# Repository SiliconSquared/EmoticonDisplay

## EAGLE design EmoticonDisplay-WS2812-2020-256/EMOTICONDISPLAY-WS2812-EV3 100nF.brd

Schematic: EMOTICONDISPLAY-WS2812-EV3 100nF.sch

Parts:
C1, C2, C3, C4, C5, C6, C7, C8, C9, C10, C11, C12, C13, C14, C15, C16, C17, C18, C19, C20, C21, C22, C23, C24, C25, C26, C27, C28, C29, C30, C31, C32, C33, C34, C35, C36, C37, C38, C39, C40, C41, C42, C43, C44, C45, C46, C47, C48, C49, C50, C51, C52, C53, C54, C55, C56, C57, C58, C59, C60, C61, C62, C63, C64, C65, C66, C67, C68, C69, C70, C71, C72, C73, C74, C75, C76, C77, C78, C79, C80, C81, C82, C83, C84, C85, C86, C87, C88, C89, C90, C91, C92, C93, C94, C95, C96, C97, C98, C99, C100, C101, C102, C103, C104, C105, C106, C107, C108, C109, C110, C111, C112, C113, C114, C115, C116, C117, C118, C119, C120, C121, C122, C123, C124, C125, C126, C127, C128, C129, C130, C131, C132, C133, C134, C135, C136, C137, C138, C139, C140, C141, C142, C143, C144, C145, C146, C147, C148, C149, C150, C151, C152, C153, C154, C155, C156, C157, C158, C159, C160, C161, C162, C163, C164, C165, C166, C167, C168, C169, C170, C171, C172, C173, C174, C175, C176, C177, C178, C179, C180, C181, C182, C183, C184, C185, C186, C187, C188, C189, C190, C191, C192, C193, C194, C195, C196, C197, C198, C199, C200, C201, C202, C203, C204, C205, C206, C207, C208, C209, C210, C211, C212, C213, C214, C215, C216, C217, C218, C219, C220, C221, C222, C223, C224, C225, C226, C227, C228, C229, C230, C231, C232, C233, C234, C235, C236, C237, C238, C239, C240, C241, C242, C243, C244, C245, C246, C247, C248, C249, C250, C251, C252, C253, C254, C255, C256: 100nF; C-0402
CAP15: 1uF 10%; C-0402
FAULT: RED; CHIPLED_0603
GNDA: TPTP15R; TP15R
GNDB: TPTP15R; TP15R
JP2: HEADER-1X5ROUND; 1X05_ROUND
R1: 22k; 0603-NO
R2: 220 1%; 0603-NO
R4: 100k; R0402
R6: 10k; R0402
R8: 1k; R0402
R11: 0; 0603-NO
RGB1, RGB2, RGB3, RGB4, RGB5, RGB6, RGB7, RGB8, RGB9, RGB10, RGB11, RGB12, RGB13, RGB14, RGB15, RGB16, RGB17, RGB18, RGB19, RGB20, RGB21, RGB22, RGB23, RGB24, RGB25, RGB26, RGB27, RGB28, RGB29, RGB30, RGB31, RGB32, RGB33, RGB34, RGB35, RGB36, RGB37, RGB38, RGB39, RGB40, RGB41, RGB42, RGB43, RGB44, RGB45, RGB46, RGB47, RGB48, RGB49, RGB50, RGB51, RGB52, RGB53, RGB54, RGB55, RGB56, RGB57, RGB58, RGB59, RGB60, RGB61, RGB62, RGB63, RGB64, RGB65, RGB66, RGB67, RGB68, RGB69, RGB70, RGB71, RGB72, RGB73, RGB74, RGB75, RGB76, RGB77, RGB78, RGB79, RGB80, RGB81, RGB82, RGB83, RGB84, RGB85, RGB86, RGB87, RGB88, RGB89, RGB90, RGB91, RGB92, RGB93, RGB94, RGB95, RGB96, RGB97, RGB98, RGB99, RGB100, RGB101, RGB102, RGB103, RGB104, RGB105, RGB106, RGB107, RGB108, RGB109, RGB110, RGB111, RGB112, RGB113, RGB114, RGB115, RGB116, RGB117, RGB118, RGB119, RGB120, RGB121, RGB122, RGB123, RGB124, RGB125, RGB126, RGB127, RGB128, RGB129, RGB130, RGB131, RGB132, RGB133, RGB134, RGB135, RGB136, RGB137, RGB138, RGB139, RGB140, RGB141, RGB142, RGB143, RGB144, RGB145, RGB146, RGB147, RGB148, RGB149, RGB150, RGB151, RGB152, RGB153, RGB154, RGB155, RGB156, RGB157, RGB158, RGB159, RGB160, RGB161, RGB162, RGB163, RGB164, RGB165, RGB166, RGB167, RGB168, RGB169, RGB170, RGB171, RGB172, RGB173, RGB174, RGB175, RGB176, RGB177, RGB178, RGB179, RGB180, RGB181, RGB182, RGB183, RGB184, RGB185, RGB186, RGB187, RGB188, RGB189, RGB190, RGB191, RGB192, RGB193, RGB194, RGB195, RGB196, RGB197, RGB198, RGB199, RGB200, RGB201, RGB202, RGB203, RGB204, RGB205, RGB206, RGB207, RGB208, RGB209, RGB210, RGB211, RGB212, RGB213, RGB214, RGB215, RGB216, RGB217, RGB218, RGB219, RGB220, RGB221, RGB222, RGB223, RGB224, RGB225, RGB226, RGB227, RGB228, RGB229, RGB230, RGB231, RGB232, RGB233, RGB234, RGB235, RGB236, RGB237, RGB238, RGB239, RGB240, RGB241, RGB242, RGB243, RGB244, RGB245, RGB246, RGB247, RGB248, RGB249, RGB250, RGB251, RGB252, RGB253, RGB254, RGB255, RGB256: WS2812-2020; LED_WS2812-2020
U1: NCP380LMUAJAATBG; UDFN-6
U2: SN74LVC1T45; SOT23-6
U3: PRTR5V0U2X; SOT-143B

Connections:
ENABLE: JP2.2, R6.1, U1.4 (!EN)
FLAG: FAULT.C, R4.1, U1.3 (!FLAG)
GND: C1.2, C2.2, C3.2, C4.2, C5.2, C6.2, C7.2, C8.2, C9.2, C10.2, C11.2, C12.2, C13.2, C14.2, C15.2, C16.2, C17.2, C18.2, C19.2, C20.2, C21.2, C22.2, C23.2, C24.2, C25.2, C26.2, C27.2, C28.2, C29.2, C30.2, C31.2, C32.2, C33.2, C34.2, C35.2, C36.2, C37.2, C38.2, C39.2, C40.2, C41.2, C42.2, C43.2, C44.2, C45.2, C46.2, C47.2, C48.2, C49.2, C50.2, C51.2, C52.2, C53.2, C54.2, C55.2, C56.2, C57.2, C58.2, C59.2, C60.2, C61.2, C62.2, C63.2, C64.2, C65.2, C66.2, C67.2, C68.2, C69.2, C70.2, C71.2, C72.2, C73.2, C74.2, C75.2, C76.2, C77.2, C78.2, C79.2, C80.2, C81.2, C82.2, C83.2, C84.2, C85.2, C86.2, C87.2, C88.2, C89.2, C90.2, C91.2, C92.2, C93.2, C94.2, C95.2, C96.2, C97.2, C98.2, C99.2, C100.2, C101.2, C102.2, C103.2, C104.2, C105.2, C106.2, C107.2, C108.2, C109.2, C110.2, C111.2, C112.2, C113.2, C114.2, C115.2, C116.2, C117.2, C118.2, C119.2, C120.2, C121.2, C122.2, C123.2, C124.2, C125.2, C126.2, C127.2, C128.2, C129.2, C130.2, C131.2, C132.2, C133.2, C134.2, C135.2, C136.2, C137.2, C138.2, C139.2, C140.2, C141.2, C142.2, C143.2, C144.2, C145.2, C146.2, C147.2, C148.2, C149.2, C150.2, C151.2, C152.2, C153.2, C154.2, C155.2, C156.2, C157.2, C158.2, C159.2, C160.2, C161.2, C162.2, C163.2, C164.2, C165.2, C166.2, C167.2, C168.2, C169.2, C170.2, C171.2, C172.2, C173.2, C174.2, C175.2, C176.2, C177.2, C178.2, C179.2, C180.2, C181.2, C182.2, C183.2, C184.2, C185.2, C186.2, C187.2, C188.2, C189.2, C190.2, C191.2, C192.2, C193.2, C194.2, C195.2, C196.2, C197.2, C198.2, C199.2, C200.2, C201.2, C202.2, C203.2, C204.2, C205.2, C206.2, C207.2, C208.2, C209.2, C210.2, C211.2, C212.2, C213.2, C214.2, C215.2, C216.2, C217.2, C218.2, C219.2, C220.2, C221.2, C222.2, C223.2, C224.2, C225.2, C226.2, C227.2, C228.2, C229.2, C230.2, C231.2, C232.2, C233.2, C234.2, C235.2, C236.2, C237.2, C238.2, C239.2, C240.2, C241.2, C242.2, C243.2, C244.2, C245.2, C246.2, C247.2, C248.2, C249.2, C250.2, C251.2, C252.2, C253.2, C254.2, C255.2, C256.2, CAP15.2, GNDA.TP, GNDB.TP, JP2.4, R1.2, R6.2, RGB1.2 (GND), RGB2.2 (GND), RGB3.2 (GND), RGB4.2 (GND), RGB5.2 (GND), RGB6.2 (GND), RGB7.2 (GND), RGB8.2 (GND), RGB9.2 (GND), RGB10.2 (GND), RGB11.2 (GND), RGB12.2 (GND), RGB13.2 (GND), RGB14.2 (GND), RGB15.2 (GND), RGB16.2 (GND), RGB17.2 (GND), RGB18.2 (GND), RGB19.2 (GND), RGB20.2 (GND), RGB21.2 (GND), RGB22.2 (GND), RGB23.2 (GND), RGB24.2 (GND), RGB25.2 (GND), RGB26.2 (GND), RGB27.2 (GND), RGB28.2 (GND), RGB29.2 (GND), RGB30.2 (GND), RGB31.2 (GND), RGB32.2 (GND), RGB33.2 (GND), RGB34.2 (GND), RGB35.2 (GND), RGB36.2 (GND), RGB37.2 (GND), RGB38.2 (GND), RGB39.2 (GND), RGB40.2 (GND), RGB41.2 (GND), RGB42.2 (GND), RGB43.2 (GND), RGB44.2 (GND), RGB45.2 (GND), RGB46.2 (GND), RGB47.2 (GND), RGB48.2 (GND), RGB49.2 (GND), RGB50.2 (GND), RGB51.2 (GND), RGB52.2 (GND), RGB53.2 (GND), RGB54.2 (GND), RGB55.2 (GND), RGB56.2 (GND), RGB57.2 (GND), RGB58.2 (GND), RGB59.2 (GND), RGB60.2 (GND), RGB61.2 (GND), RGB62.2 (GND), RGB63.2 (GND), RGB64.2 (GND), RGB65.2 (GND), RGB66.2 (GND), RGB67.2 (GND), RGB68.2 (GND), RGB69.2 (GND), RGB70.2 (GND), RGB71.2 (GND), RGB72.2 (GND), RGB73.2 (GND), RGB74.2 (GND), RGB75.2 (GND), RGB76.2 (GND), RGB77.2 (GND), RGB78.2 (GND), RGB79.2 (GND), RGB80.2 (GND), RGB81.2 (GND), RGB82.2 (GND), RGB83.2 (GND), RGB84.2 (GND), RGB85.2 (GND), RGB86.2 (GND), RGB87.2 (GND), RGB88.2 (GND), RGB89.2 (GND), RGB90.2 (GND), RGB91.2 (GND), RGB92.2 (GND), RGB93.2 (GND), RGB94.2 (GND), RGB95.2 (GND), RGB96.2 (GND), RGB97.2 (GND), RGB98.2 (GND), RGB99.2 (GND), RGB100.2 (GND), RGB101.2 (GND), RGB102.2 (GND), RGB103.2 (GND), RGB104.2 (GND), RGB105.2 (GND), RGB106.2 (GND), RGB107.2 (GND), RGB108.2 (GND), RGB109.2 (GND), RGB110.2 (GND), RGB111.2 (GND), RGB112.2 (GND), RGB113.2 (GND), RGB114.2 (GND), RGB115.2 (GND), RGB116.2 (GND), RGB117.2 (GND), RGB118.2 (GND), RGB119.2 (GND), RGB120.2 (GND), RGB121.2 (GND), RGB122.2 (GND), RGB123.2 (GND), RGB124.2 (GND), RGB125.2 (GND), RGB126.2 (GND), RGB127.2 (GND), RGB128.2 (GND), RGB129.2 (GND), RGB130.2 (GND), RGB131.2 (GND), RGB132.2 (GND), RGB133.2 (GND), RGB134.2 (GND), RGB135.2 (GND), RGB136.2 (GND), RGB137.2 (GND), RGB138.2 (GND), RGB139.2 (GND), RGB140.2 (GND), RGB141.2 (GND), RGB142.2 (GND), RGB143.2 (GND), RGB144.2 (GND), RGB145.2 (GND), RGB146.2 (GND), RGB147.2 (GND), RGB148.2 (GND), RGB149.2 (GND), RGB150.2 (GND), RGB151.2 (GND), RGB152.2 (GND), RGB153.2 (GND), RGB154.2 (GND), RGB155.2 (GND), RGB156.2 (GND), RGB157.2 (GND), RGB158.2 (GND), RGB159.2 (GND), RGB160.2 (GND), RGB161.2 (GND), RGB162.2 (GND), RGB163.2 (GND), RGB164.2 (GND), RGB165.2 (GND), RGB166.2 (GND), RGB167.2 (GND), RGB168.2 (GND), RGB169.2 (GND), RGB170.2 (GND), RGB171.2 (GND), RGB172.2 (GND), RGB173.2 (GND), RGB174.2 (GND), RGB175.2 (GND), RGB176.2 (GND), RGB177.2 (GND), RGB178.2 (GND), RGB179.2 (GND), RGB180.2 (GND), RGB181.2 (GND), RGB182.2 (GND), RGB183.2 (GND), RGB184.2 (GND), RGB185.2 (GND), RGB186.2 (GND), RGB187.2 (GND), RGB188.2 (GND), RGB189.2 (GND), RGB190.2 (GND), RGB191.2 (GND), RGB192.2 (GND), RGB193.2 (GND), RGB194.2 (GND), RGB195.2 (GND), RGB196.2 (GND), RGB197.2 (GND), RGB198.2 (GND), RGB199.2 (GND), RGB200.2 (GND), RGB201.2 (GND), RGB202.2 (GND), RGB203.2 (GND), RGB204.2 (GND), RGB205.2 (GND), RGB206.2 (GND), RGB207.2 (GND), RGB208.2 (GND), RGB209.2 (GND), RGB210.2 (GND), RGB211.2 (GND), RGB212.2 (GND), RGB213.2 (GND), RGB214.2 (GND), RGB215.2 (GND), RGB216.2 (GND), RGB217.2 (GND), RGB218.2 (GND), RGB219.2 (GND), RGB220.2 (GND), RGB221.2 (GND), RGB222.2 (GND), RGB223.2 (GND), RGB224.2 (GND), RGB225.2 (GND), RGB226.2 (GND), RGB227.2 (GND), RGB228.2 (GND), RGB229.2 (GND), RGB230.2 (GND), RGB231.2 (GND), RGB232.2 (GND), RGB233.2 (GND), RGB234.2 (GND), RGB235.2 (GND), RGB236.2 (GND), RGB237.2 (GND), RGB238.2 (GND), RGB239.2 (GND), RGB240.2 (GND), RGB241.2 (GND), RGB242.2 (GND), RGB243.2 (GND), RGB244.2 (GND), RGB245.2 (GND), RGB246.2 (GND), RGB247.2 (GND), RGB248.2 (GND), RGB249.2 (GND), RGB250.2 (GND), RGB251.2 (GND), RGB252.2 (GND), RGB253.2 (GND), RGB254.2 (GND), RGB255.2 (GND), RGB256.2 (GND), U1.5 (GND), U1.PAD (GND), U2.2 (GND), U2.5 (DIR), U3.1 (GND)
HOST-PIXDIN: JP2.5, R2.2, U3.3 (IO2)
LLIN-PIXDIN: R2.1, R11.1, U2.4 (B)
unnamed: RGB1.1 (DO), RGB2.3 (DI)
unnamed: RGB2.1 (DO), RGB3.3 (DI)
unnamed: RGB3.1 (DO), RGB4.3 (DI)
unnamed: RGB4.1 (DO), RGB5.3 (DI)
unnamed: RGB5.1 (DO), RGB6.3 (DI)
unnamed: RGB7.1 (DO), RGB8.3 (DI)
unnamed: RGB8.1 (DO), RGB9.3 (DI)
unnamed: RGB9.1 (DO), RGB10.3 (DI)
unnamed: RGB10.1 (DO), RGB11.3 (DI)
unnamed: RGB11.1 (DO), RGB12.3 (DI)
unnamed: RGB12.1 (DO), RGB13.3 (DI)
unnamed: R1.1, U1.2 (ILIM)
unnamed: RGB13.1 (DO), RGB14.3 (DI)
unnamed: RGB14.1 (DO), RGB15.3 (DI)
unnamed: RGB15.1 (DO), RGB16.3 (DI)
unnamed: RGB23.1 (DO), RGB24.3 (DI)
unnamed: RGB6.1 (DO), RGB7.3 (DI)
unnamed: RGB42.1 (DO), RGB43.3 (DI)
unnamed: RGB27.1 (DO), RGB28.3 (DI)
unnamed: RGB18.1 (DO), RGB19.3 (DI)
unnamed: RGB26.1 (DO), RGB27.3 (DI)
unnamed: RGB25.1 (DO), RGB26.3 (DI)
unnamed: RGB24.1 (DO), RGB25.3 (DI)
unnamed: RGB22.1 (DO), RGB23.3 (DI)
unnamed: RGB21.1 (DO), RGB22.3 (DI)
unnamed: RGB20.1 (DO), RGB21.3 (DI)
unnamed: RGB19.1 (DO), RGB20.3 (DI)
unnamed: RGB17.1 (DO), RGB18.3 (DI)
unnamed: RGB16.1 (DO), RGB17.3 (DI)
unnamed: RGB58.1 (DO), RGB59.3 (DI)
unnamed: RGB41.1 (DO), RGB42.3 (DI)
unnamed: RGB40.1 (DO), RGB41.3 (DI)
unnamed: RGB39.1 (DO), RGB40.3 (DI)
unnamed: RGB38.1 (DO), RGB39.3 (DI)
unnamed: RGB37.1 (DO), RGB38.3 (DI)
unnamed: RGB36.1 (DO), RGB37.3 (DI)
unnamed: RGB35.1 (DO), RGB36.3 (DI)
unnamed: RGB34.1 (DO), RGB35.3 (DI)
unnamed: RGB33.1 (DO), RGB34.3 (DI)
unnamed: RGB32.1 (DO), RGB33.3 (DI)
unnamed: RGB31.1 (DO), RGB32.3 (DI)
unnamed: RGB30.1 (DO), RGB31.3 (DI)
unnamed: RGB29.1 (DO), RGB30.3 (DI)
unnamed: RGB28.1 (DO), RGB29.3 (DI)
unnamed: RGB43.1 (DO), RGB44.3 (DI)
unnamed: RGB44.1 (DO), RGB45.3 (DI)
unnamed: RGB45.1 (DO), RGB46.3 (DI)
unnamed: RGB46.1 (DO), RGB47.3 (DI)
unnamed: RGB47.1 (DO), RGB48.3 (DI)
unnamed: RGB48.1 (DO), RGB49.3 (DI)
unnamed: RGB49.1 (DO), RGB50.3 (DI)
unnamed: RGB50.1 (DO), RGB51.3 (DI)
unnamed: RGB51.1 (DO), RGB52.3 (DI)
unnamed: RGB52.1 (DO), RGB53.3 (DI)
unnamed: RGB53.1 (DO), RGB54.3 (DI)
unnamed: RGB54.1 (DO), RGB55.3 (DI)
unnamed: RGB55.1 (DO), RGB56.3 (DI)
unnamed: RGB56.1 (DO), RGB57.3 (DI)
unnamed: RGB75.1 (DO), RGB76.3 (DI)
unnamed: RGB59.1 (DO), RGB60.3 (DI)
unnamed: RGB57.1 (DO), RGB58.3 (DI)
unnamed: RGB60.1 (DO), RGB61.3 (DI)
unnamed: RGB61.1 (DO), RGB62.3 (DI)
unnamed: RGB62.1 (DO), RGB63.3 (DI)
unnamed: RGB63.1 (DO), RGB64.3 (DI)
unnamed: RGB64.1 (DO), RGB65.3 (DI)
unnamed: RGB65.1 (DO), RGB66.3 (DI)
unnamed: RGB66.1 (DO), RGB67.3 (DI)
unnamed: RGB67.1 (DO), RGB68.3 (DI)
unnamed: RGB68.1 (DO), RGB69.3 (DI)
unnamed: RGB69.1 (DO), RGB70.3 (DI)
unnamed: RGB70.1 (DO), RGB71.3 (DI)
unnamed: RGB71.1 (DO), RGB72.3 (DI)
unnamed: RGB72.1 (DO), RGB73.3 (DI)
unnamed: RGB73.1 (DO), RGB74.3 (DI)
unnamed: RGB74.1 (DO), RGB75.3 (DI)
unnamed: RGB121.1 (DO), RGB122.3 (DI)
unnamed: RGB122.1 (DO), RGB123.3 (DI)
unnamed: RGB76.1 (DO), RGB77.3 (DI)
unnamed: RGB77.1 (DO), RGB78.3 (DI)
unnamed: RGB78.1 (DO), RGB79.3 (DI)
unnamed: RGB79.1 (DO), RGB80.3 (DI)
unnamed: RGB80.1 (DO), RGB81.3 (DI)
unnamed: RGB81.1 (DO), RGB82.3 (DI)
unnamed: RGB82.1 (DO), RGB83.3 (DI)
unnamed: RGB83.1 (DO), RGB84.3 (DI)
unnamed: RGB84.1 (DO), RGB85.3 (DI)
unnamed: RGB85.1 (DO), RGB86.3 (DI)
unnamed: RGB86.1 (DO), RGB87.3 (DI)
unnamed: RGB87.1 (DO), RGB88.3 (DI)
unnamed: RGB88.1 (DO), RGB89.3 (DI)
unnamed: RGB89.1 (DO), RGB90.3 (DI)
unnamed: RGB90.1 (DO), RGB91.3 (DI)
unnamed: RGB91.1 (DO), RGB92.3 (DI)
unnamed: RGB123.1 (DO), RGB124.3 (DI)
unnamed: RGB93.1 (DO), RGB94.3 (DI)
unnamed: RGB94.1 (DO), RGB95.3 (DI)
unnamed: RGB95.1 (DO), RGB96.3 (DI)
unnamed: RGB96.1 (DO), RGB97.3 (DI)
unnamed: RGB97.1 (DO), RGB98.3 (DI)
unnamed: RGB98.1 (DO), RGB99.3 (DI)
unnamed: RGB99.1 (DO), RGB100.3 (DI)
unnamed: RGB100.1 (DO), RGB101.3 (DI)
unnamed: RGB101.1 (DO), RGB102.3 (DI)
unnamed: RGB102.1 (DO), RGB103.3 (DI)
unnamed: RGB103.1 (DO), RGB104.3 (DI)
unnamed: RGB104.1 (DO), RGB105.3 (DI)
unnamed: RGB105.1 (DO), RGB106.3 (DI)
unnamed: RGB106.1 (DO), RGB107.3 (DI)
unnamed: RGB107.1 (DO), RGB108.3 (DI)
unnamed: RGB108.1 (DO), RGB109.3 (DI)
unnamed: RGB109.1 (DO), RGB110.3 (DI)
unnamed: RGB198.1 (DO), RGB199.3 (DI)
unnamed: RGB92.1 (DO), RGB93.3 (DI)
unnamed: RGB124.1 (DO), RGB125.3 (DI)
unnamed: RGB111.1 (DO), RGB112.3 (DI)
unnamed: RGB112.1 (DO), RGB113.3 (DI)
unnamed: RGB113.1 (DO), RGB114.3 (DI)
unnamed: RGB114.1 (DO), RGB115.3 (DI)
unnamed: RGB115.1 (DO), RGB116.3 (DI)
unnamed: RGB116.1 (DO), RGB117.3 (DI)
unnamed: RGB117.1 (DO), RGB118.3 (DI)
unnamed: RGB118.1 (DO), RGB119.3 (DI)
unnamed: RGB119.1 (DO), RGB120.3 (DI)
unnamed: RGB120.1 (DO), RGB121.3 (DI)
unnamed: RGB125.1 (DO), RGB126.3 (DI)
unnamed: RGB126.1 (DO), RGB127.3 (DI)
unnamed: RGB127.1 (DO), RGB128.3 (DI)
unnamed: RGB110.1 (DO), RGB111.3 (DI)
unnamed: RGB164.1 (DO), RGB165.3 (DI)
unnamed: RGB214.1 (DO), RGB215.3 (DI)
unnamed: RGB147.1 (DO), RGB148.3 (DI)
unnamed: RGB129.1 (DO), RGB130.3 (DI)
unnamed: RGB130.1 (DO), RGB131.3 (DI)
unnamed: RGB131.1 (DO), RGB132.3 (DI)
unnamed: RGB132.1 (DO), RGB133.3 (DI)
unnamed: RGB133.1 (DO), RGB134.3 (DI)
unnamed: RGB134.1 (DO), RGB135.3 (DI)
unnamed: RGB135.1 (DO), RGB136.3 (DI)
unnamed: RGB136.1 (DO), RGB137.3 (DI)
unnamed: RGB137.1 (DO), RGB138.3 (DI)
unnamed: RGB138.1 (DO), RGB139.3 (DI)
unnamed: RGB139.1 (DO), RGB140.3 (DI)
unnamed: RGB140.1 (DO), RGB141.3 (DI)
unnamed: RGB141.1 (DO), RGB142.3 (DI)
unnamed: RGB142.1 (DO), RGB143.3 (DI)
unnamed: RGB143.1 (DO), RGB144.3 (DI)
unnamed: RGB144.1 (DO), RGB145.3 (DI)
unnamed: RGB145.1 (DO), RGB146.3 (DI)
unnamed: RGB128.1 (DO), RGB129.3 (DI)
unnamed: RGB148.1 (DO), RGB149.3 (DI)
unnamed: RGB149.1 (DO), RGB150.3 (DI)
unnamed: RGB150.1 (DO), RGB151.3 (DI)
unnamed: RGB151.1 (DO), RGB152.3 (DI)
unnamed: RGB152.1 (DO), RGB153.3 (DI)
unnamed: RGB153.1 (DO), RGB154.3 (DI)
unnamed: RGB154.1 (DO), RGB155.3 (DI)
unnamed: RGB155.1 (DO), RGB156.3 (DI)
unnamed: RGB156.1 (DO), RGB157.3 (DI)
unnamed: RGB157.1 (DO), RGB158.3 (DI)
unnamed: RGB158.1 (DO), RGB159.3 (DI)
unnamed: RGB159.1 (DO), RGB160.3 (DI)
unnamed: RGB160.1 (DO), RGB161.3 (DI)
unnamed: RGB161.1 (DO), RGB162.3 (DI)
unnamed: RGB162.1 (DO), RGB163.3 (DI)
unnamed: RGB163.1 (DO), RGB164.3 (DI)
unnamed: RGB146.1 (DO), RGB147.3 (DI)
unnamed: RGB165.1 (DO), RGB166.3 (DI)
unnamed: RGB166.1 (DO), RGB167.3 (DI)
unnamed: RGB167.1 (DO), RGB168.3 (DI)
unnamed: RGB168.1 (DO), RGB169.3 (DI)
unnamed: RGB169.1 (DO), RGB170.3 (DI)
unnamed: RGB170.1 (DO), RGB171.3 (DI)
unnamed: RGB171.1 (DO), RGB172.3 (DI)
unnamed: RGB172.1 (DO), RGB173.3 (DI)
unnamed: RGB173.1 (DO), RGB174.3 (DI)
unnamed: RGB174.1 (DO), RGB175.3 (DI)
unnamed: RGB175.1 (DO), RGB176.3 (DI)
unnamed: RGB176.1 (DO), RGB177.3 (DI)
unnamed: RGB177.1 (DO), RGB178.3 (DI)
unnamed: RGB178.1 (DO), RGB179.3 (DI)
unnamed: RGB179.1 (DO), RGB180.3 (DI)
unnamed: RGB180.1 (DO), RGB181.3 (DI)
unnamed: RGB181.1 (DO), RGB182.3 (DI)
unnamed: RGB230.1 (DO), RGB231.3 (DI)
unnamed: RGB183.1 (DO), RGB184.3 (DI)
unnamed: RGB184.1 (DO), RGB185.3 (DI)
unnamed: RGB185.1 (DO), RGB186.3 (DI)
unnamed: RGB186.1 (DO), RGB187.3 (DI)
unnamed: RGB187.1 (DO), RGB188.3 (DI)
unnamed: RGB188.1 (DO), RGB189.3 (DI)
unnamed: RGB189.1 (DO), RGB190.3 (DI)
unnamed: RGB190.1 (DO), RGB191.3 (DI)
unnamed: RGB191.1 (DO), RGB192.3 (DI)
unnamed: RGB192.1 (DO), RGB193.3 (DI)
unnamed: RGB193.1 (DO), RGB194.3 (DI)
unnamed: RGB194.1 (DO), RGB195.3 (DI)
unnamed: RGB195.1 (DO), RGB196.3 (DI)
unnamed: RGB196.1 (DO), RGB197.3 (DI)
unnamed: RGB197.1 (DO), RGB198.3 (DI)
unnamed: RGB182.1 (DO), RGB183.3 (DI)
unnamed: RGB199.1 (DO), RGB200.3 (DI)
unnamed: RGB200.1 (DO), RGB201.3 (DI)
unnamed: RGB201.1 (DO), RGB202.3 (DI)
unnamed: RGB202.1 (DO), RGB203.3 (DI)
unnamed: RGB203.1 (DO), RGB204.3 (DI)
unnamed: RGB204.1 (DO), RGB205.3 (DI)
unnamed: RGB205.1 (DO), RGB206.3 (DI)
unnamed: RGB206.1 (DO), RGB207.3 (DI)
unnamed: RGB207.1 (DO), RGB208.3 (DI)
unnamed: RGB208.1 (DO), RGB209.3 (DI)
unnamed: RGB209.1 (DO), RGB210.3 (DI)
unnamed: RGB210.1 (DO), RGB211.3 (DI)
unnamed: RGB211.1 (DO), RGB212.3 (DI)
unnamed: RGB212.1 (DO), RGB213.3 (DI)
unnamed: RGB213.1 (DO), RGB214.3 (DI)
unnamed: RGB215.1 (DO), RGB216.3 (DI)
unnamed: RGB216.1 (DO), RGB217.3 (DI)
unnamed: RGB217.1 (DO), RGB218.3 (DI)
unnamed: RGB218.1 (DO), RGB219.3 (DI)
unnamed: RGB219.1 (DO), RGB220.3 (DI)
unnamed: RGB220.1 (DO), RGB221.3 (DI)
unnamed: RGB221.1 (DO), RGB222.3 (DI)
unnamed: RGB222.1 (DO), RGB223.3 (DI)
unnamed: RGB223.1 (DO), RGB224.3 (DI)
unnamed: RGB224.1 (DO), RGB225.3 (DI)
unnamed: RGB225.1 (DO), RGB226.3 (DI)
unnamed: RGB226.1 (DO), RGB227.3 (DI)
unnamed: RGB227.1 (DO), RGB228.3 (DI)
unnamed: RGB231.1 (DO), RGB232.3 (DI)
unnamed: RGB229.1 (DO), RGB230.3 (DI)
unnamed: RGB232.1 (DO), RGB233.3 (DI)
unnamed: RGB233.1 (DO), RGB234.3 (DI)
unnamed: RGB234.1 (DO), RGB235.3 (DI)
unnamed: RGB235.1 (DO), RGB236.3 (DI)
unnamed: RGB236.1 (DO), RGB237.3 (DI)
unnamed: RGB237.1 (DO), RGB238.3 (DI)
unnamed: RGB238.1 (DO), RGB239.3 (DI)
unnamed: RGB239.1 (DO), RGB240.3 (DI)
unnamed: RGB228.1 (DO), RGB229.3 (DI)
unnamed: RGB240.1 (DO), RGB241.3 (DI)
unnamed: FAULT.A, R8.2
unnamed: RGB241.1 (DO), RGB242.3 (DI)
unnamed: RGB242.1 (DO), RGB243.3 (DI)
unnamed: RGB243.1 (DO), RGB244.3 (DI)
unnamed: RGB244.1 (DO), RGB245.3 (DI)
unnamed: RGB245.1 (DO), RGB246.3 (DI)
unnamed: RGB246.1 (DO), RGB247.3 (DI)
unnamed: RGB247.1 (DO), RGB248.3 (DI)
unnamed: RGB248.1 (DO), RGB249.3 (DI)
unnamed: RGB249.1 (DO), RGB250.3 (DI)
unnamed: RGB251.1 (DO), RGB252.3 (DI)
unnamed: RGB252.1 (DO), RGB253.3 (DI)
unnamed: RGB253.1 (DO), RGB254.3 (DI)
unnamed: RGB254.1 (DO), RGB255.3 (DI)
unnamed: RGB255.1 (DO), RGB256.3 (DI)
unnamed: RGB250.1 (DO), RGB251.3 (DI)
PIXDIN: R11.2, RGB1.3 (DI), U2.3 (A)
VDD: C1.1, C2.1, C3.1, C4.1, C5.1, C6.1, C7.1, C8.1, C9.1, C10.1, C11.1, C12.1, C13.1, C14.1, C15.1, C16.1, C17.1, C18.1, C19.1, C20.1, C21.1, C22.1, C23.1, C24.1, C25.1, C26.1, C27.1, C28.1, C29.1, C30.1, C31.1, C32.1, C33.1, C34.1, C35.1, C36.1, C37.1, C38.1, C39.1, C40.1, C41.1, C42.1, C43.1, C44.1, C45.1, C46.1, C47.1, C48.1, C49.1, C50.1, C51.1, C52.1, C53.1, C54.1, C55.1, C56.1, C57.1, C58.1, C59.1, C60.1, C61.1, C62.1, C63.1, C64.1, C65.1, C66.1, C67.1, C68.1, C69.1, C70.1, C71.1, C72.1, C73.1, C74.1, C75.1, C76.1, C77.1, C78.1, C79.1, C80.1, C81.1, C82.1, C83.1, C84.1, C85.1, C86.1, C87.1, C88.1, C89.1, C90.1, C91.1, C92.1, C93.1, C94.1, C95.1, C96.1, C97.1, C98.1, C99.1, C100.1, C101.1, C102.1, C103.1, C104.1, C105.1, C106.1, C107.1, C108.1, C109.1, C110.1, C111.1, C112.1, C113.1, C114.1, C115.1, C116.1, C117.1, C118.1, C119.1, C120.1, C121.1, C122.1, C123.1, C124.1, C125.1, C126.1, C127.1, C128.1, C129.1, C130.1, C131.1, C132.1, C133.1, C134.1, C135.1, C136.1, C137.1, C138.1, C139.1, C140.1, C141.1, C142.1, C143.1, C144.1, C145.1, C146.1, C147.1, C148.1, C149.1, C150.1, C151.1, C152.1, C153.1, C154.1, C155.1, C156.1, C157.1, C158.1, C159.1, C160.1, C161.1, C162.1, C163.1, C164.1, C165.1, C166.1, C167.1, C168.1, C169.1, C170.1, C171.1, C172.1, C173.1, C174.1, C175.1, C176.1, C177.1, C178.1, C179.1, C180.1, C181.1, C182.1, C183.1, C184.1, C185.1, C186.1, C187.1, C188.1, C189.1, C190.1, C191.1, C192.1, C193.1, C194.1, C195.1, C196.1, C197.1, C198.1, C199.1, C200.1, C201.1, C202.1, C203.1, C204.1, C205.1, C206.1, C207.1, C208.1, C209.1, C210.1, C211.1, C212.1, C213.1, C214.1, C215.1, C216.1, C217.1, C218.1, C219.1, C220.1, C221.1, C222.1, C223.1, C224.1, C225.1, C226.1, C227.1, C228.1, C229.1, C230.1, C231.1, C232.1, C233.1, C234.1, C235.1, C236.1, C237.1, C238.1, C239.1, C240.1, C241.1, C242.1, C243.1, C244.1, C245.1, C246.1, C247.1, C248.1, C249.1, C250.1, C251.1, C252.1, C253.1, C254.1, C255.1, C256.1, RGB1.4 (VDD), RGB2.4 (VDD), RGB3.4 (VDD), RGB4.4 (VDD), RGB5.4 (VDD), RGB6.4 (VDD), RGB7.4 (VDD), RGB8.4 (VDD), RGB9.4 (VDD), RGB10.4 (VDD), RGB11.4 (VDD), RGB12.4 (VDD), RGB13.4 (VDD), RGB14.4 (VDD), RGB15.4 (VDD), RGB16.4 (VDD), RGB17.4 (VDD), RGB18.4 (VDD), RGB19.4 (VDD), RGB20.4 (VDD), RGB21.4 (VDD), RGB22.4 (VDD), RGB23.4 (VDD), RGB24.4 (VDD), RGB25.4 (VDD), RGB26.4 (VDD), RGB27.4 (VDD), RGB28.4 (VDD), RGB29.4 (VDD), RGB30.4 (VDD), RGB31.4 (VDD), RGB32.4 (VDD), RGB33.4 (VDD), RGB34.4 (VDD), RGB35.4 (VDD), RGB36.4 (VDD), RGB37.4 (VDD), RGB38.4 (VDD), RGB39.4 (VDD), RGB40.4 (VDD), RGB41.4 (VDD), RGB42.4 (VDD), RGB43.4 (VDD), RGB44.4 (VDD), RGB45.4 (VDD), RGB46.4 (VDD), RGB47.4 (VDD), RGB48.4 (VDD), RGB49.4 (VDD), RGB50.4 (VDD), RGB51.4 (VDD), RGB52.4 (VDD), RGB53.4 (VDD), RGB54.4 (VDD), RGB55.4 (VDD), RGB56.4 (VDD), RGB57.4 (VDD), RGB58.4 (VDD), RGB59.4 (VDD), RGB60.4 (VDD), RGB61.4 (VDD), RGB62.4 (VDD), RGB63.4 (VDD), RGB64.4 (VDD), RGB65.4 (VDD), RGB66.4 (VDD), RGB67.4 (VDD), RGB68.4 (VDD), RGB69.4 (VDD), RGB70.4 (VDD), RGB71.4 (VDD), RGB72.4 (VDD), RGB73.4 (VDD), RGB74.4 (VDD), RGB75.4 (VDD), RGB76.4 (VDD), RGB77.4 (VDD), RGB78.4 (VDD), RGB79.4 (VDD), RGB80.4 (VDD), RGB81.4 (VDD), RGB82.4 (VDD), RGB83.4 (VDD), RGB84.4 (VDD), RGB85.4 (VDD), RGB86.4 (VDD), RGB87.4 (VDD), RGB88.4 (VDD), RGB89.4 (VDD), RGB90.4 (VDD), RGB91.4 (VDD), RGB92.4 (VDD), RGB93.4 (VDD), RGB94.4 (VDD), RGB95.4 (VDD), RGB96.4 (VDD), RGB97.4 (VDD), RGB98.4 (VDD), RGB99.4 (VDD), RGB100.4 (VDD), RGB101.4 (VDD), RGB102.4 (VDD), RGB103.4 (VDD), RGB104.4 (VDD), RGB105.4 (VDD), RGB106.4 (VDD), RGB107.4 (VDD), RGB108.4 (VDD), RGB109.4 (VDD), RGB110.4 (VDD), RGB111.4 (VDD), RGB112.4 (VDD), RGB113.4 (VDD), RGB114.4 (VDD), RGB115.4 (VDD), RGB116.4 (VDD), RGB117.4 (VDD), RGB118.4 (VDD), RGB119.4 (VDD), RGB120.4 (VDD), RGB121.4 (VDD), RGB122.4 (VDD), RGB123.4 (VDD), RGB124.4 (VDD), RGB125.4 (VDD), RGB126.4 (VDD), RGB127.4 (VDD), RGB128.4 (VDD), RGB129.4 (VDD), RGB130.4 (VDD), RGB131.4 (VDD), RGB132.4 (VDD), RGB133.4 (VDD), RGB134.4 (VDD), RGB135.4 (VDD), RGB136.4 (VDD), RGB137.4 (VDD), RGB138.4 (VDD), RGB139.4 (VDD), RGB140.4 (VDD), RGB141.4 (VDD), RGB142.4 (VDD), RGB143.4 (VDD), RGB144.4 (VDD), RGB145.4 (VDD), RGB146.4 (VDD), RGB147.4 (VDD), RGB148.4 (VDD), RGB149.4 (VDD), RGB150.4 (VDD), RGB151.4 (VDD), RGB152.4 (VDD), RGB153.4 (VDD), RGB154.4 (VDD), RGB155.4 (VDD), RGB156.4 (VDD), RGB157.4 (VDD), RGB158.4 (VDD), RGB159.4 (VDD), RGB160.4 (VDD), RGB161.4 (VDD), RGB162.4 (VDD), RGB163.4 (VDD), RGB164.4 (VDD), RGB165.4 (VDD), RGB166.4 (VDD), RGB167.4 (VDD), RGB168.4 (VDD), RGB169.4 (VDD), RGB170.4 (VDD), RGB171.4 (VDD), RGB172.4 (VDD), RGB173.4 (VDD), RGB174.4 (VDD), RGB175.4 (VDD), RGB176.4 (VDD), RGB177.4 (VDD), RGB178.4 (VDD), RGB179.4 (VDD), RGB180.4 (VDD), RGB181.4 (VDD), RGB182.4 (VDD), RGB183.4 (VDD), RGB184.4 (VDD), RGB185.4 (VDD), RGB186.4 (VDD), RGB187.4 (VDD), RGB188.4 (VDD), RGB189.4 (VDD), RGB190.4 (VDD), RGB191.4 (VDD), RGB192.4 (VDD), RGB193.4 (VDD), RGB194.4 (VDD), RGB195.4 (VDD), RGB196.4 (VDD), RGB197.4 (VDD), RGB198.4 (VDD), RGB199.4 (VDD), RGB200.4 (VDD), RGB201.4 (VDD), RGB202.4 (VDD), RGB203.4 (VDD), RGB204.4 (VDD), RGB205.4 (VDD), RGB206.4 (VDD), RGB207.4 (VDD), RGB208.4 (VDD), RGB209.4 (VDD), RGB210.4 (VDD), RGB211.4 (VDD), RGB212.4 (VDD), RGB213.4 (VDD), RGB214.4 (VDD), RGB215.4 (VDD), RGB216.4 (VDD), RGB217.4 (VDD), RGB218.4 (VDD), RGB219.4 (VDD), RGB220.4 (VDD), RGB221.4 (VDD), RGB222.4 (VDD), RGB223.4 (VDD), RGB224.4 (VDD), RGB225.4 (VDD), RGB226.4 (VDD), RGB227.4 (VDD), RGB228.4 (VDD), RGB229.4 (VDD), RGB230.4 (VDD), RGB231.4 (VDD), RGB232.4 (VDD), RGB233.4 (VDD), RGB234.4 (VDD), RGB235.4 (VDD), RGB236.4 (VDD), RGB237.4 (VDD), RGB238.4 (VDD), RGB239.4 (VDD), RGB240.4 (VDD), RGB241.4 (VDD), RGB242.4 (VDD), RGB243.4 (VDD), RGB244.4 (VDD), RGB245.4 (VDD), RGB246.4 (VDD), RGB247.4 (VDD), RGB248.4 (VDD), RGB249.4 (VDD), RGB250.4 (VDD), RGB251.4 (VDD), RGB252.4 (VDD), RGB253.4 (VDD), RGB254.4 (VDD), RGB255.4 (VDD), RGB256.4 (VDD), U1.1 (VOUT), U2.1 (VCCA), U2.6 (VCCB), U3.4 (VCC)
VHOST: CAP15.1, JP2.1, R4.2, R8.1, U1.6 (VIN)

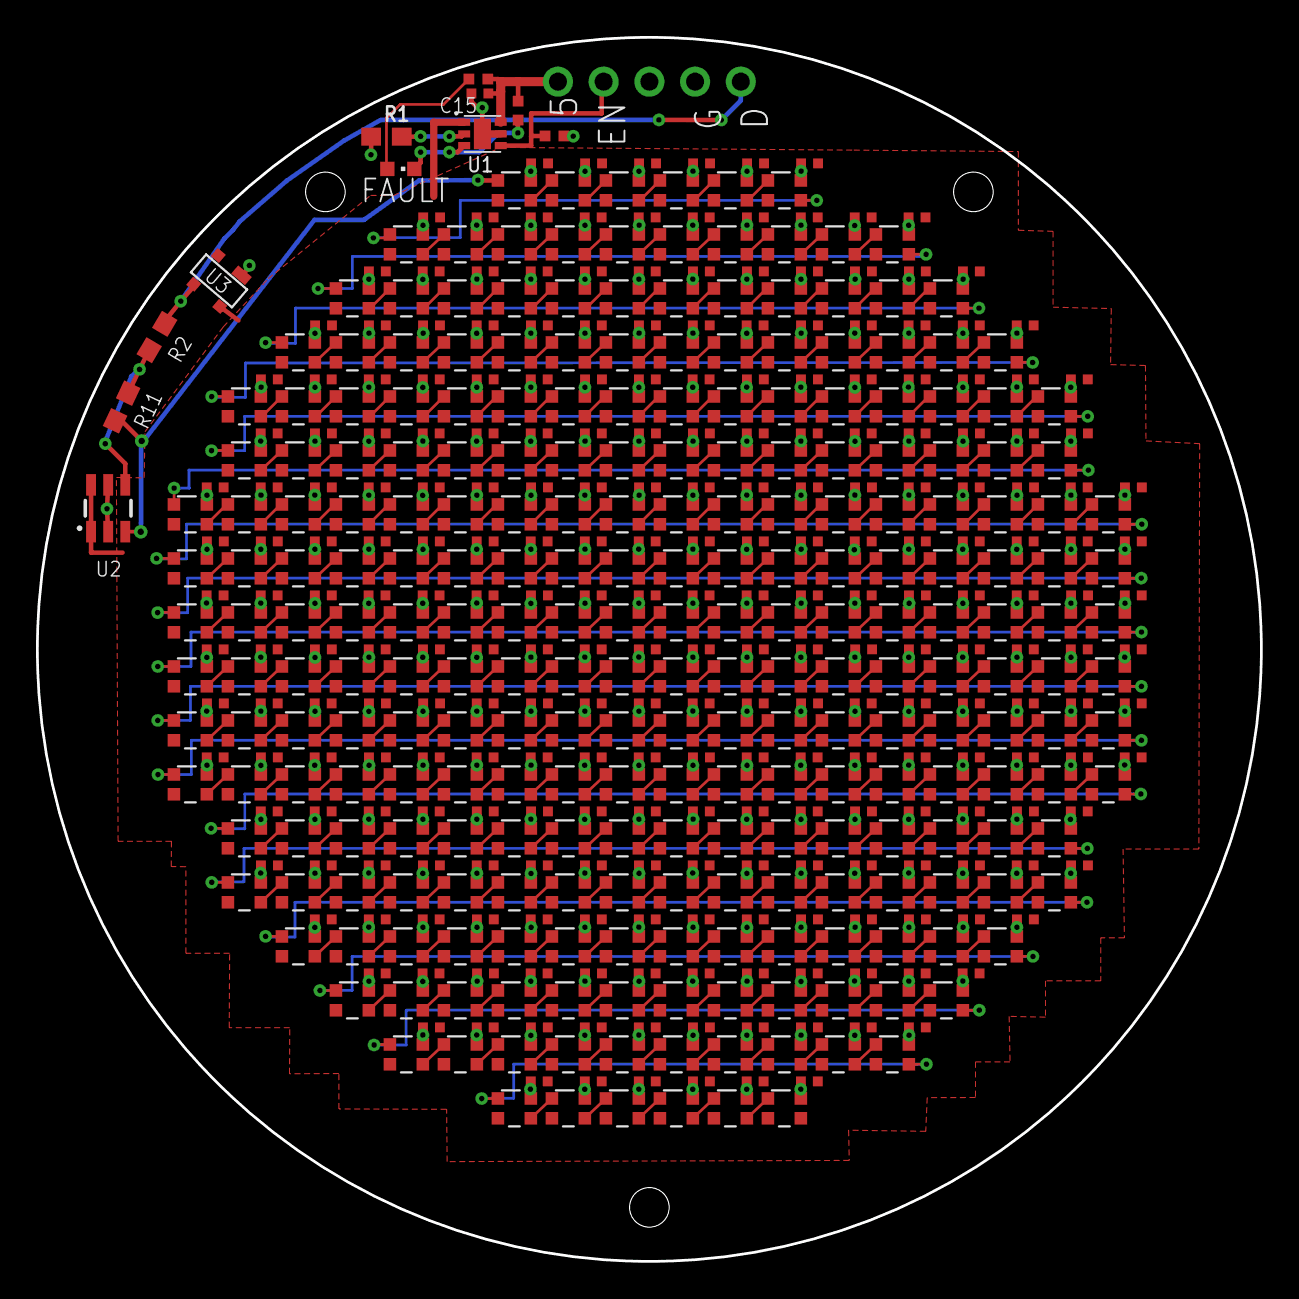
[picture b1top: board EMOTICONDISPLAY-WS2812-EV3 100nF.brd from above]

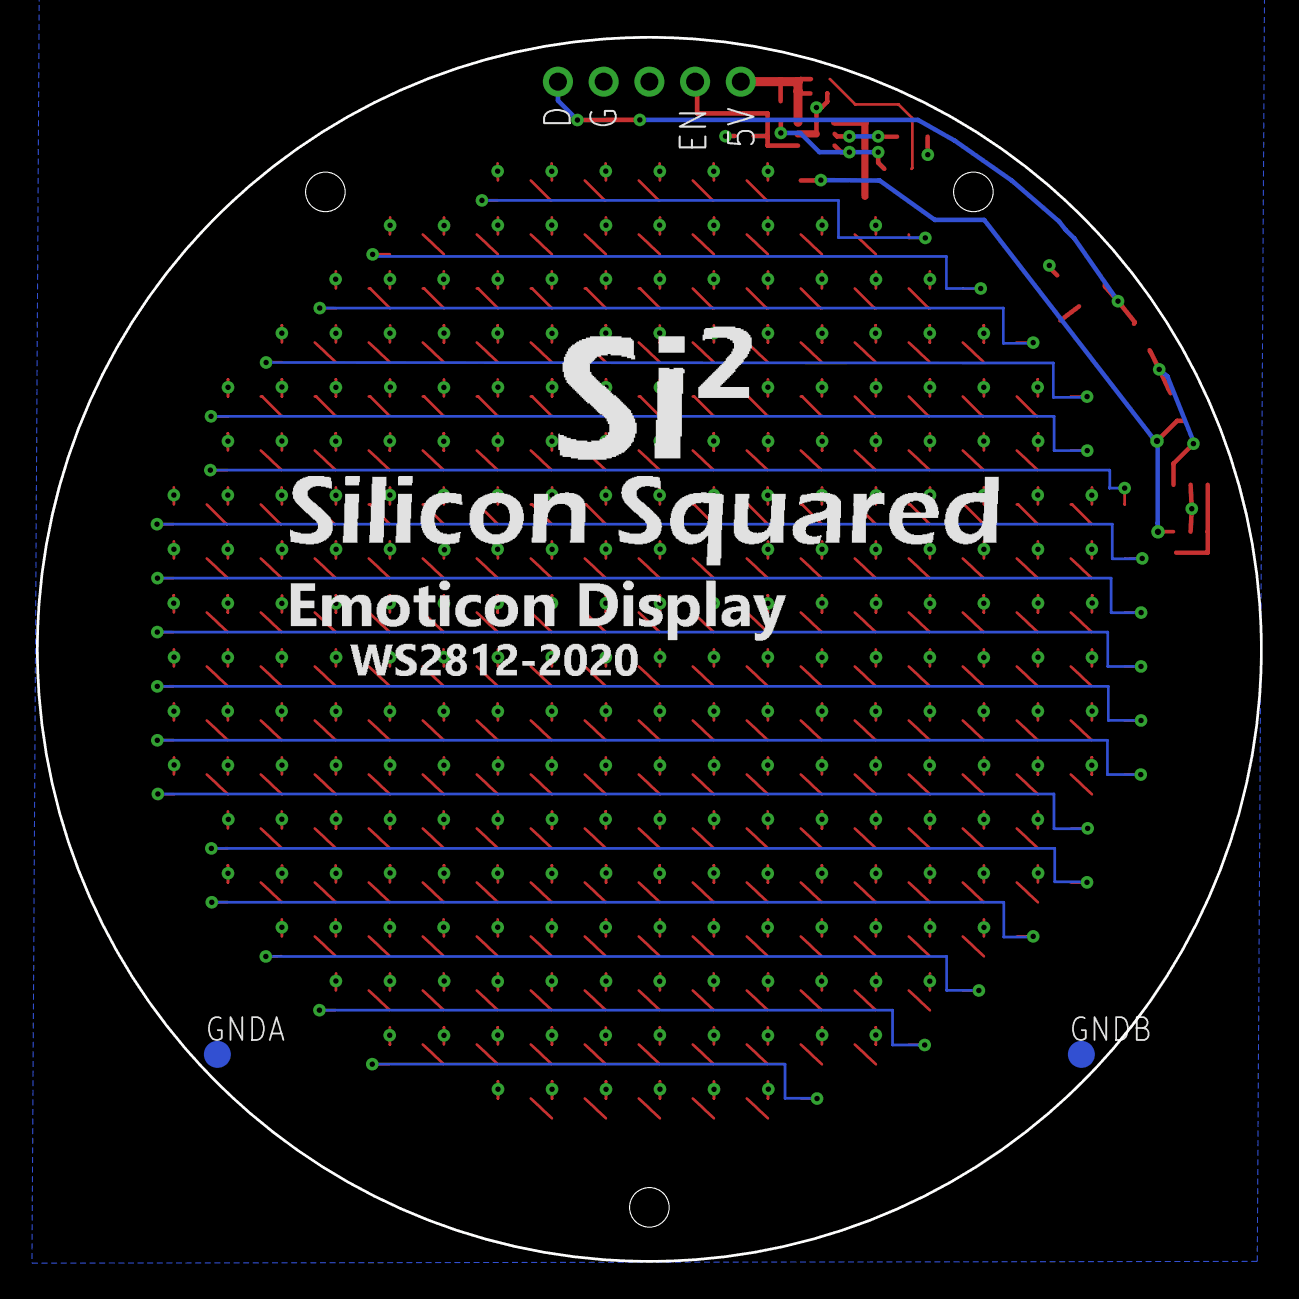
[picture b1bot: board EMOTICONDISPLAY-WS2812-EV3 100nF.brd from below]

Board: 2 copper layers, 68.0 x 68.0 mm, 526 parts (2 on the bottom side), 265 nets.

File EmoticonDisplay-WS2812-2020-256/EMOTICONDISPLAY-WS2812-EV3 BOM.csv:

Part,Value,Device,Package
C1-C256,100nF,CAP0402,C-0402
FAULT,Red,LEDCHIPLED_0603,CHIPLED_0603
R1,22k,RESISTOR_0603_NOOUT,0603-NO
R2,220 1%,RESISTOR_0603_NOOUT,0603-NO
R6,10k,RESISTOR_0603_NOOUT,0603-NO
R4,100k,RESR0402,R0402
R8,1k,RESR0402,R0402
RGB1-RGB256,WS2812-2020,WS2812-2020,LED_WS2812-2020
CAP15,1uF 10%,CAP0402,C-0402
U1,NCP380HMUAJAATBG,NCP380HMUAJAATBG,UDFN-6
U2,SN74LVC1T45,SN74LVC1T45SOT-23,SOT23-6
U3,PRTR5V0U2X,PRTR5V0U2X,SOT-143B
				
Unique Parts,	12			
Total Parts,	403

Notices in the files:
parts and their libraries:
microbuilder: This work is placed in the public domain, and may be freely used for commercial and non-commercial work with the following conditions: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
Volks: Creative Commons Attribution-ShareAlike 3.0 Unported (CC BY-SA 3.0), http://creativecommons.org/licenses/by-sa/3.0/.
